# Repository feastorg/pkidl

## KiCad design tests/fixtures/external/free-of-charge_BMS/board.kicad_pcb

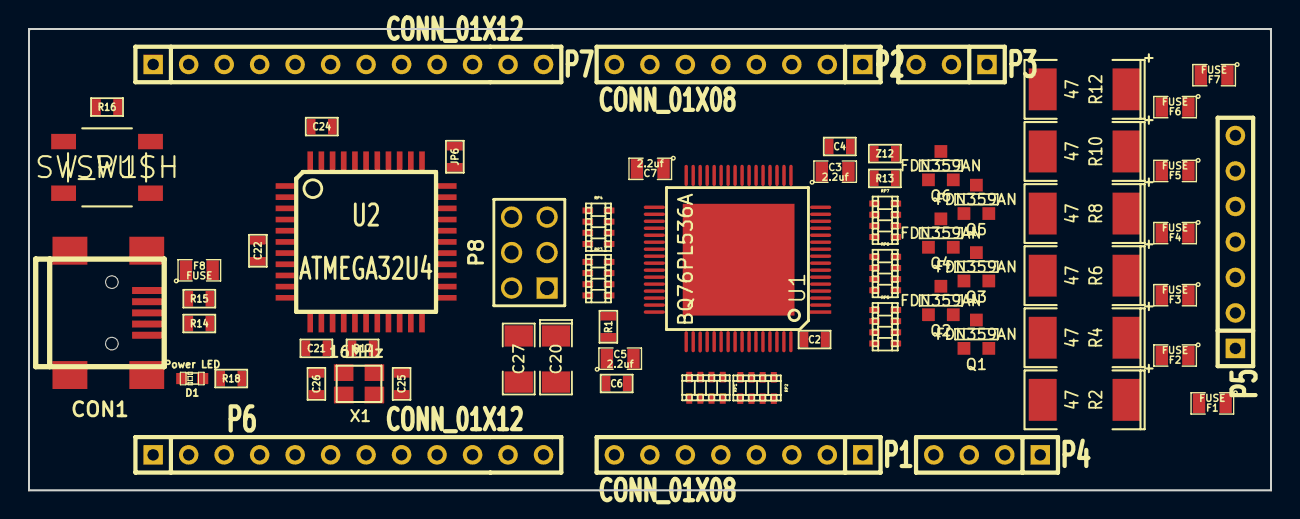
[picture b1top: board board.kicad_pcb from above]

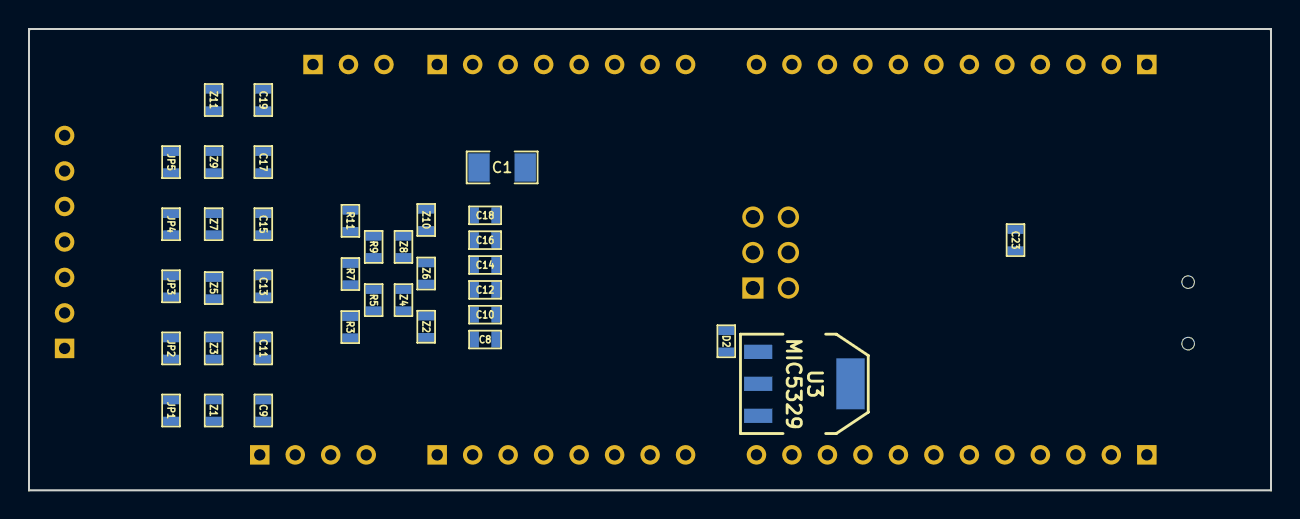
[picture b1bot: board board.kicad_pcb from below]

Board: 2 copper layers, 88.9 x 33.0 mm, 100 parts (37 on the bottom side), 118 nets, no tracks yet.

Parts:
C1, C27: 10uf; SM1206
C2, C4, C6, C8, C9, C10, C11, C12, C13, C14, C15, C16, C17, C18, C19, C21, C22, C24: 0.1uf; SM0603
C3, C5, C7: 2.2uf; SM0805
C20: 10uf; SM1206POL
C23: 1uf; SM0603
C25, C26: 20pf; SM0603
CON1: USB-MINI-B; USB_MINI_B
D1: Power LED; LED-0603
D2: DIODE; SM0603
F1, F2, F3, F4, F5, F6, F7, F8: FUSE; SM0805
JP1, JP2, JP3, JP4, JP5, JP6: JUMPER; SM0603
P1, P2: CONN_01X08; SIL-8
P3: CONN_01X03; SIL-3
P4: CONN_01X04; SIL-4
P5: CONN_01X07; SIL-7
P6, P7: CONN_01X12; SIL-12
P8: CONN_02X03; pin_array_3x2
Q1, Q2, Q3, Q4, Q5, Q6: FDN359AN; SOT23GDS
R1: 100k; SM0603
R2, R4, R6, R8, R10, R12: 47; SM2512
R3, R5, R7, R9, R11, R13: 1M 1%; SM0603
R14, R15: 22; SM0603
R16: 10k; SM0603
R17: 1M; SM0603
R18: 1k; SM0603
RP1, RP2, RP3, RP4: R_PACK4; r_cat16-4
RP5, RP6, RP7: 1k; r_cat16-4
SW1: SW_PUSH; SW
U1: BQ76PL536A; HTQFP_64
U2: ATMEGA32U4; TQFP44
U3: MIC5329; SOT223
X1: 16MHz; crystal_FA238-TSX3225
Z1, Z2, Z3, Z4, Z5, Z6, Z7, Z8, Z9, Z10, Z11, Z12: ZENER; SM0603

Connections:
+5V: C20.1, C21.1, C22.1, D2.1, F8.2, P6.1, P6.3, P7.1, P7.3, P8.2, R16.1, R18.2, U2.2, U2.7, U2.14, U2.24, U2.34, U2.44, U3.3
+BATT: C2.1, C9.1, D2.2, F1.2, JP1.1, R2.1, RP5.1, U1.63, U1.64, U3.1, Z1.2
/CellBallance/C0: F7.1, P5.7
/CellBallance/C1: F6.1, P5.6
/CellBallance/C2: F5.1, P5.5
/CellBallance/C3: F4.1, P5.4
/CellBallance/C4: F3.1, P5.3
/CellBallance/C5: F2.1, P5.2
/CellBallance/C6: F1.1, P5.1
/CellBallance/CB1: RP7.5, U1.12
/CellBallance/CB2: RP7.7, U1.10
/CellBallance/CB3: RP6.5, U1.8
/CellBallance/CB4: RP6.7, U1.6
/CellBallance/CB5: RP5.5, U1.4
/CellBallance/CB6: RP5.7, U1.2
/CellBallance/VC1: C18.2, RP7.6, U1.11
/CellBallance/VC2: C16.2, RP7.8, U1.9
/CellBallance/VC3: C14.2, RP6.6, U1.7
/CellBallance/VC4: C12.2, RP6.8, U1.5
/CellBallance/VC5: C10.2, RP5.6, U1.3
/CellBallance/VC6: C8.2, RP5.8, U1.1
/LDOA: C3.1, C4.1, U1.17
/LDOD: C5.1, C6.1, R1.2, U1.18, U1.46
/REG50: C7.1, U1.32
/VREF: C1.1, U1.16
/atmega32u4/A0: P7.10, U2.36
/atmega32u4/A1: P7.9, U2.37
/atmega32u4/A2: P7.8, U2.38
/atmega32u4/A3: P7.7, U2.39
/atmega32u4/A4: P7.6, U2.40
/atmega32u4/A5: P7.5, U2.41
/atmega32u4/ALERT_H: RP4.7, U2.1
/atmega32u4/AREF: C24.1, U2.42
/atmega32u4/CONV_H: P7.11, RP4.5, U2.31
/atmega32u4/CS_H: RP3.8, U2.30
/atmega32u4/D0/RX: P6.7, U2.20
/atmega32u4/D1/TX: P6.8, U2.21
/atmega32u4/D2/SDA: P6.6, U2.19
/atmega32u4/D3/SCL: P6.5, U2.18
/atmega32u4/D4: P6.9, U2.25
/atmega32u4/DRDY_H: P6.12, RP4.6, U2.27
/atmega32u4/FAULT_H: RP4.8, U2.29
/atmega32u4/HWB: JP6.1, U2.33
/atmega32u4/IO12: P6.11, U2.26
/atmega32u4/IO13*: P7.12, U2.32
/atmega32u4/RST: P8.5, R16.2, SW1.2, U2.13
/atmega32u4/SCLK_H: P8.3, RP3.5, U2.9
/atmega32u4/SDI_H: P8.4, RP3.7, U2.10
/atmega32u4/SDO_H: P8.1, RP3.6, U2.11
/atmega32u4/TXLED: P6.10, U2.22
/atmega32u4/UCAP: C23.1, U2.6
GND: C20.2, C21.2, C22.2, C23.2, C24.2, C25.2, C26.2, C27.2, CON1.5, CON1.6, CON1.7, CON1.8, CON1.9, D1.2, JP6.2, P6.2, P6.4, P7.2, P7.4, P8.6, SW1.1, U2.5, U2.15, U2.23, U2.35, U2.43, U3.2, U3.4, X1.3
unnamed: P2.1, U1.21
unnamed: P2.2, U1.22
unnamed: P2.3, U1.23
unnamed: P2.4, U1.24
unnamed: P2.5, U1.26
unnamed: P2.6, U1.27
unnamed: P1.3, RP2.2
unnamed: P1.2, RP2.3
unnamed: P1.1, RP2.4
unnamed: P1.4, RP2.1
unnamed: P2.7, U1.28
unnamed: P2.8, U1.29
unnamed: P1.5, RP1.4
unnamed: P1.6, RP1.3
unnamed: P1.7, RP1.2
unnamed: P1.8, RP1.1
unnamed: P3.2, U1.47
unnamed: RP1.8, U1.52
unnamed: RP1.7, U1.53
unnamed: RP1.6, U1.54
unnamed: RP1.5, U1.55
unnamed: P3.3, U1.45
unnamed: P3.1, U1.48
unnamed: P4.4, U1.60
unnamed: P4.3, U1.61
unnamed: P4.2, U1.19
unnamed: RP3.4, U1.40
unnamed: RP3.3, U1.41
unnamed: RP3.2, U1.42
unnamed: RP3.1, U1.43
unnamed: P4.1, U1.20
unnamed: RP4.4, U1.36
unnamed: RP4.3, U1.37
unnamed: RP4.2, U1.38
unnamed: RP4.1, U1.39
unnamed: RP2.8, U1.56
unnamed: RP2.7, U1.57
unnamed: RP2.6, U1.58
unnamed: RP2.5, U1.59
unnamed: R1.1, U1.44
unnamed: Q1.G, R3.1, RP5.2, Z2.2
unnamed: Q1.D, R2.2
unnamed: Q2.D, R4.2
unnamed: Q6.G, R13.1, RP7.4, Z12.2
unnamed: Q4.G, R9.1, RP6.4, Z8.2
unnamed: Q5.D, R10.2
unnamed: Q5.G, R11.1, RP7.2, Z10.2
unnamed: Q3.G, R7.1, RP6.2, Z6.2
unnamed: C13.2, C15.1, F4.2, JP3.2, JP4.1, Q3.S, R7.2, R8.1, RP6.3, Z5.1, Z6.1, Z7.2
unnamed: Q2.G, R5.1, RP5.4, Z4.2
unnamed: C15.2, C17.1, F5.2, JP4.2, JP5.1, Q4.S, R9.2, R10.1, RP7.1, Z7.1, Z8.1, Z9.2
unnamed: C17.2, C19.1, F6.2, JP5.2, Q5.S, R11.2, R12.1, RP7.3, Z9.1, Z10.1, Z11.2
unnamed: Q6.D, R12.2
unnamed: C11.2, C13.1, F3.2, JP2.2, JP3.1, Q2.S, R5.2, R6.1, RP6.1, Z3.1, Z4.1, Z5.2
unnamed: C9.2, C11.1, F2.2, JP1.2, JP2.1, Q1.S, R3.2, R4.1, RP5.3, Z1.1, Z2.1, Z3.2
unnamed: Q4.D, R8.2
unnamed: Q3.D, R6.2
unnamed: CON1.1, F8.1
unnamed: R15.2, U2.4
unnamed: R14.2, U2.3
unnamed: CON1.2, R15.1
unnamed: C26.1, R17.2, U2.16, X1.2
unnamed: C25.1, R17.1, U2.17, X1.1
unnamed: D1.1, R18.1
unnamed: CON1.3, R14.1
VSS: C1.2, C2.2, C3.2, C4.2, C5.2, C6.2, C7.2, C8.1, C10.1, C12.1, C14.1, C16.1, C18.1, C19.2, F7.2, Q6.S, R13.2, U1.0, U1.13, U1.14, U1.15, U1.25, U1.33, U1.34, U1.35, U1.49, U1.50, Z11.1, Z12.1
